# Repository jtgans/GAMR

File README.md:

This is an electronics hacking project that involves building
a [TerasIC DE0-Nano FPGA board][TerasIC] into a simplistic, fun, and
retargetable handheld gaming console.

[TerasIC]: http://www.terasic.com.tw/cgi-bin/page/archive.pl?Language=English&CategoryNo=139&No=593&PartNo=1

## Design

The console consists of three major parts:

  - The Left and Right controller (both using the same components and basic
    schematic -- only the board art is different)
  - The TFT LCD backlight, power, and audio amp board
  - Adapters for the speakers

This repository contains the Eagle 8.x projects, the Altera Cyclone IV VHDL
source code for the cores, as well as a few bits of software written for the
console.

## Spirit of the Project

The idea is to make this as drop-dead simple to build as possible, minus the
fabbing of the boards. As a result, it'll use mostly through-hole components,
0608-class SMT parts if absolutely necessary, and 0.1" headers wherever
interconnects are required. Everything should be hand-assembleable by someone
with minimal electronics experience without expensive rework stations.

Component counts should be kept as minimal as possible. Anything that could
typically be done using a piece of discrete hardware (say, a SID chip, or a
fancy DAC, video controller, CPU, etc.) should ideally be done in the FPGA to
keep things as simple and malleable as possible.

The boards included in this repository will likely be built using OSHpark
or some other OSS-friendly project, so just look for the "GAMR" acronym in their
catalogs.

As of this writing, the following boards are now in production:

  * [Left Controller][left-controller]
  * [Right Controller][right-controller]

[left-controller]: https://oshpark.com/shared_projects/AXFgIkdE
[right-controller]: https://oshpark.com/shared_projects/QkbYnFhj

## Why "GAMR"? What's it mean?

I dunno. PiGrrl, GameGrrl, FPGamer... GAMR. Doesn't really mean anything -- I
needed a name, so I chose that. =o)

## License

This project is placed under the WTFPL. You can do what the f--- you'd like with
it. Depending on whether or not more people get involved, I may change this to
something more sane if folks would like to collaborate more. One thing to note:
I'm not planning on making money on it, but maybe you can on Tindie. =o)

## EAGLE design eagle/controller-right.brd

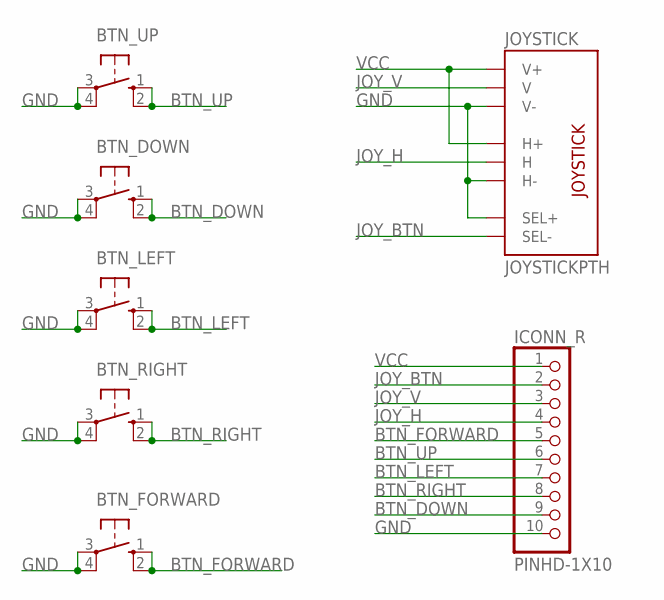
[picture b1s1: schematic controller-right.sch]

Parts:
BTN_DOWN: 40-XX-ROUND; B3F-40XX-ROUND
BTN_FORWARD: 40-XX-ROUND; B3F-40XX-ROUND
BTN_LEFT: 40-XX-ROUND; B3F-40XX-ROUND
BTN_RIGHT: 40-XX-ROUND; B3F-40XX-ROUND
BTN_UP: 40-XX-ROUND; B3F-40XX-ROUND
ICONN_R: PINHD-1X10; 1X10-BIG
JOYSTICK: JOYSTICKPTH; JOYSTICK

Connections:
BTN_DOWN: BTN_DOWN.1 (S), BTN_DOWN.2 (S1), ICONN_R.9
BTN_FORWARD: BTN_FORWARD.1 (S), BTN_FORWARD.2 (S1), ICONN_R.5
BTN_LEFT: BTN_LEFT.1 (S), BTN_LEFT.2 (S1), ICONN_R.7
BTN_RIGHT: BTN_RIGHT.1 (S), BTN_RIGHT.2 (S1), ICONN_R.8
BTN_UP: BTN_UP.1 (S), BTN_UP.2 (S1), ICONN_R.6
GND: BTN_DOWN.3, BTN_DOWN.4 (P1), BTN_FORWARD.3, BTN_FORWARD.4 (P1), BTN_LEFT.3, BTN_LEFT.4 (P1), BTN_RIGHT.3, BTN_RIGHT.4 (P1), BTN_UP.3, BTN_UP.4 (P1), ICONN_R.10, JOYSTICK.B1A (SEL+), JOYSTICK.H3 (H-), JOYSTICK.V3 (V-)
JOY_BTN: ICONN_R.2, JOYSTICK.B2A (SEL-)
JOY_H: ICONN_R.4, JOYSTICK.H2 (H)
JOY_V: ICONN_R.3, JOYSTICK.V2 (V)
VCC: ICONN_R.1, JOYSTICK.H1 (H+), JOYSTICK.V1 (V+)

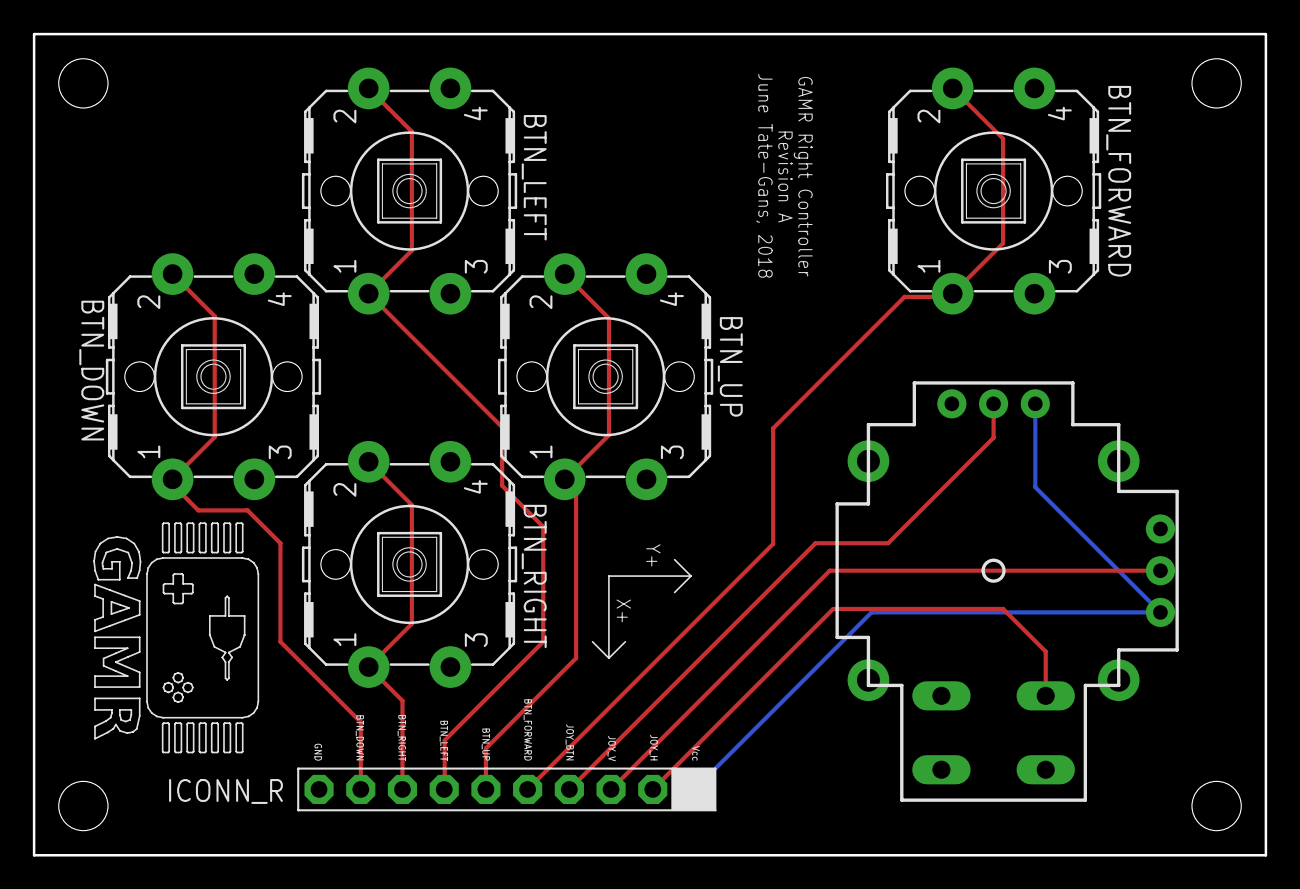
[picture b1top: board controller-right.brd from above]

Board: 2 copper layers, 75.0 x 50.0 mm, 7 parts (0 on the bottom side), 10 nets.

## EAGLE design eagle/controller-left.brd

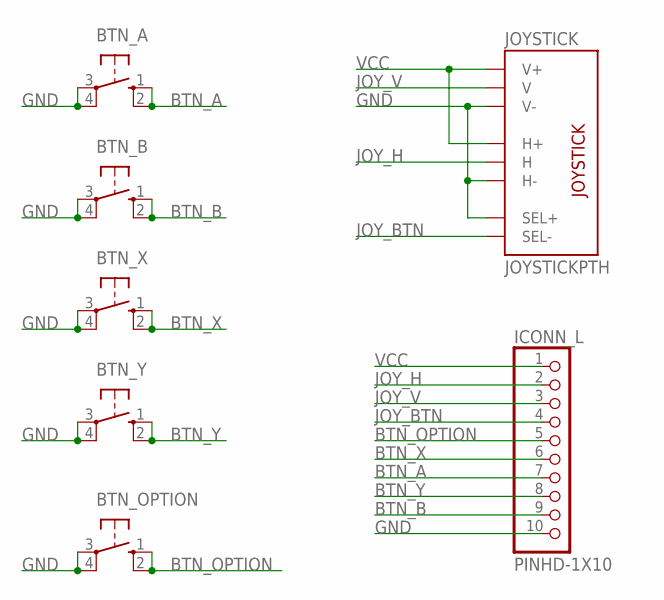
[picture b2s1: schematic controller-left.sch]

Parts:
BTN_A: 40-XX-ROUND; B3F-40XX-ROUND
BTN_B: 40-XX-ROUND; B3F-40XX-ROUND
BTN_OPTION: 40-XX-ROUND; B3F-40XX-ROUND
BTN_X: 40-XX-ROUND; B3F-40XX-ROUND
BTN_Y: 40-XX-ROUND; B3F-40XX-ROUND
ICONN_L: PINHD-1X10; 1X10-BIG
JOYSTICK: JOYSTICKPTH; JOYSTICK

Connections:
BTN_A: BTN_A.1 (S), BTN_A.2 (S1), ICONN_L.7
BTN_B: BTN_B.1 (S), BTN_B.2 (S1), ICONN_L.9
BTN_OPTION: BTN_OPTION.1 (S), BTN_OPTION.2 (S1), ICONN_L.5
BTN_X: BTN_X.1 (S), BTN_X.2 (S1), ICONN_L.6
BTN_Y: BTN_Y.1 (S), BTN_Y.2 (S1), ICONN_L.8
GND: BTN_A.3, BTN_A.4 (P1), BTN_B.3, BTN_B.4 (P1), BTN_OPTION.3, BTN_OPTION.4 (P1), BTN_X.3, BTN_X.4 (P1), BTN_Y.3, BTN_Y.4 (P1), ICONN_L.10, JOYSTICK.B1A (SEL+), JOYSTICK.H3 (H-), JOYSTICK.V3 (V-)
JOY_BTN: ICONN_L.4, JOYSTICK.B2A (SEL-)
JOY_H: ICONN_L.2, JOYSTICK.H2 (H)
JOY_V: ICONN_L.3, JOYSTICK.V2 (V)
VCC: ICONN_L.1, JOYSTICK.H1 (H+), JOYSTICK.V1 (V+)

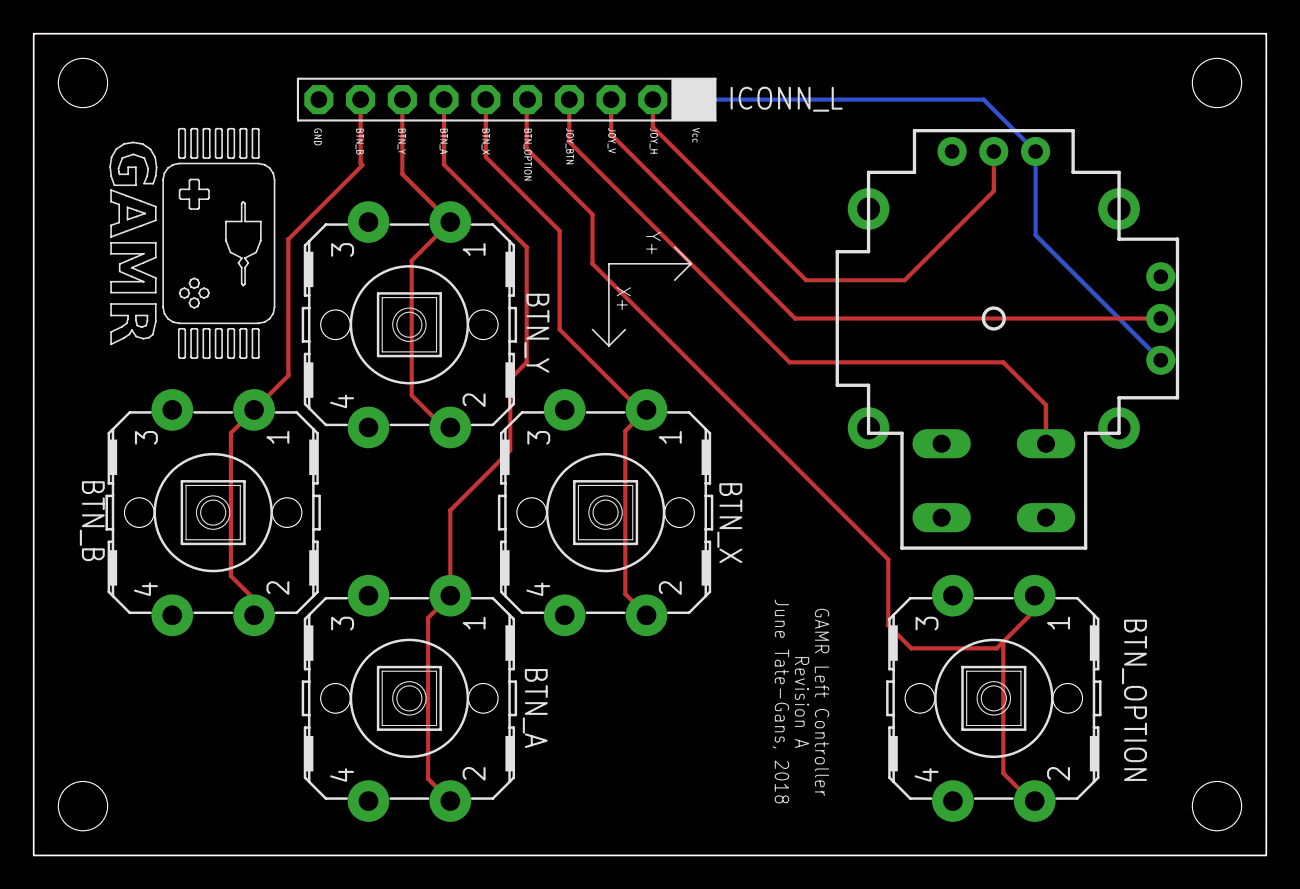
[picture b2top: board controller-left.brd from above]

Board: 2 copper layers, 75.0 x 50.0 mm, 7 parts (0 on the bottom side), 10 nets.

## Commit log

2018-01-28 controllers: Adding the left controller and logos
    Draws out the first version of the left controller board, the Eagle
    project file, and also a bunch of logos that I'll be using in the
    project.
2018-01-28 Adding a readme.
2018-01-28 Fixing the path in the readme to the logo.
2018-01-28 cleanups: Moving stuff around fixing logos, etc.
    This moves the eagle project into its own directory, fixes up the logos
    a bit, and fixes the README.md file a bit more to match up with the new
    heirarchy.
2018-01-28 logo: More fixes to the logo
2018-01-28 readme: Final tweak.
2018-01-28 gitignore: Stop tracking backup files.
2018-01-28 left-controller: Fix some silkscreen issues.
2018-01-28 left-controller: Routing adjustments
    The previews for the routing of lines inside the omron tactile switches
    was a bit too tight for the copper pour. Moved them away from some of
    the pads to compensate.
    Also minor silkscreen touches to indicate pin 1 on the ICONN_L header.
    Should prevent misorientation of the interconnects.
2018-01-28 controller: Adding in the rev. A right controller
    This adds in the right controller to the tree.
2018-01-28 bom: Adding in a bill of materials
2018-01-28 bom: Adding in more parts I missed
    Adding in additional info about the components and where to get them.
2018-01-28 bom: More info on jumper cables
    General info on how to make cables that don't suck.
2018-01-28 readme: more tweaks, info on oshpark builds
2018-01-28 readme: final tweaks for a while
2018-01-28 logo: Fix the notted AND-gate
    Seriously. A notted AND is /not/ a NAND. This ditches it in favor of a
    NOR gate, which is just as good. I wanted something like that to
    symbolize the NOR logic embedded in FPGAs.
